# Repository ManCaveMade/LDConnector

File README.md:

## LDConnector
Copyright Mitchell A. Cox (mitch@enox.co.za)

If you use this design, please acknowledge me in any resulting publications.

### Note

v1.0 doesn't seem to work with high frequency. This is probably because the RF is connected to the case, which sucks.
v2.0 is redesigned to work with a bias driver that is on the GND side of the LD. This is "normal".
 
Designed with Eagle 7.7

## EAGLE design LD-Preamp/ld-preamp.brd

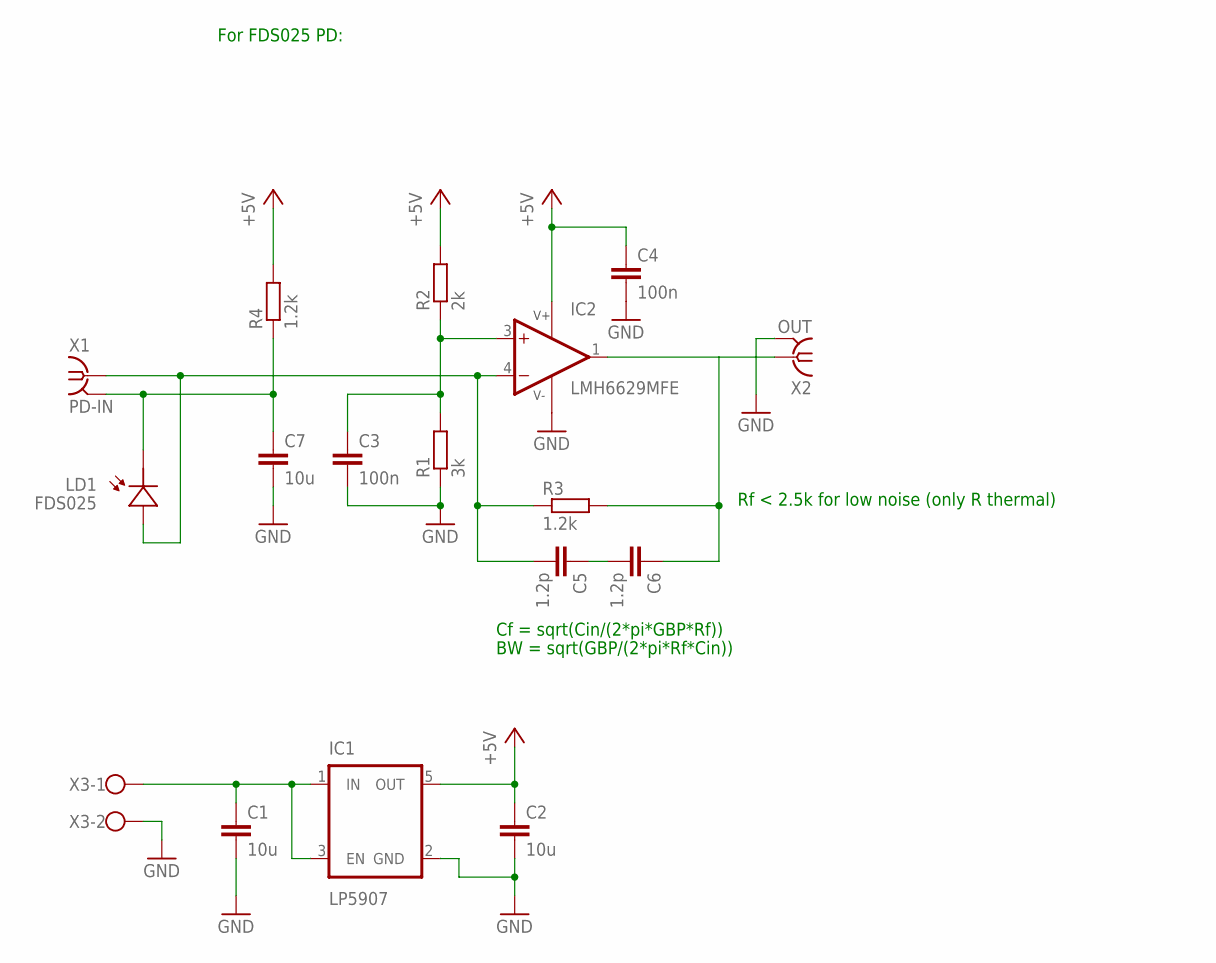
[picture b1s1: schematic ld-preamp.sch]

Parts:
C1, C2, C7: 10u; C0805
C3, C4: 100n; C0603
C5, C6: 1.2p; C0603
IC1: LP5907; SOT23-5
IC2: LMH6629MFE; SOT23-5
LD1: FDS025; PD-TO46-EDGE
R1: 3k; R0603
R2: 2k; R0603
R3, R4: 1.2k; R0603
X1: PD-IN; J502-ND-142-0711-821/826
X2: OUT; J502-ND-142-0711-821/826
X3: W237-102

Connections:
+5V: C2.1, C4.1, IC1.5 (OUT), IC2.5 (V+), R2.2, R4.2
GND: C1.2, C2.2, C3.2, C4.2, C7.2, IC1.2 (GND), IC2.2 (V-), R1.1, X2.G@1 (2), X2.G@2 (2), X2.G@3 (2), X2.G@4 (2), X3.2
unnamed: C1.1, IC1.1 (IN), IC1.3 (EN), X3.1
unnamed: C3.1, IC2.3 (+IN), R1.2, R2.1
unnamed: C5.2, IC2.4 (-IN), LD1.3 (PDA), R3.1, X1.1
unnamed: C5.1, C6.2
unnamed: C6.1, IC2.1 (OUT), R3.2, X2.1
unnamed: C7.1, LD1.1 (PDC), R4.1, X1.G@1 (2), X1.G@2 (2), X1.G@3 (2), X1.G@4 (2)

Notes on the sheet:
Cf = sqrt(Cin/(2*pi*GBP*Rf))
BW = sqrt(GBP/(2*pi*Rf*Cin))
Rf < 2.5k for low noise (only R thermal)
For FDS025 PD:

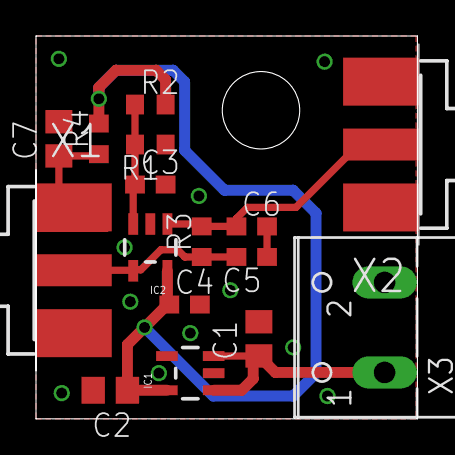
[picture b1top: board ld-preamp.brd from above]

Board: 2 copper layers, 21.3 x 21.3 mm, 17 parts (0 on the bottom side), 8 nets.

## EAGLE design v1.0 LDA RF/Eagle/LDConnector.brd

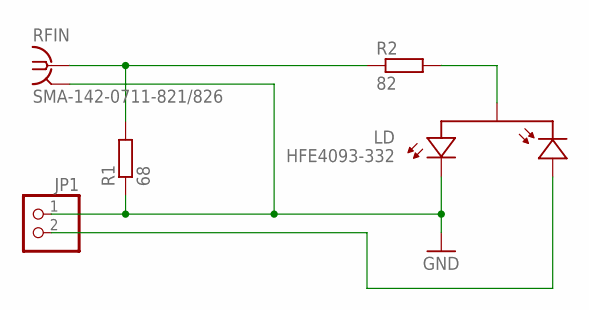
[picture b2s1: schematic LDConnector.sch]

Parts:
JP1: PINHD-1X2/90; 1X02/90
LD: HFE4093-332; HFE4093-332-EDGE
R1: 68; R0603
R2: 82; R0603
RFIN: SMA-142-0711-821/826; J502-ND-142-0711-821/826

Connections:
GND: JP1.1, LD.1-LD-CATHODE (LDC), R1.1, RFIN.G@1 (2), RFIN.G@2 (2), RFIN.G@3 (2), RFIN.G@4 (2)
unnamed: LD.2-PD-CATHODE-LD-ANO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 (LDA-PDC), R2.2
unnamed: R1.2, R2.1, RFIN.1
unnamed: JP1.2, LD.3-PD-ANODE (PDA)

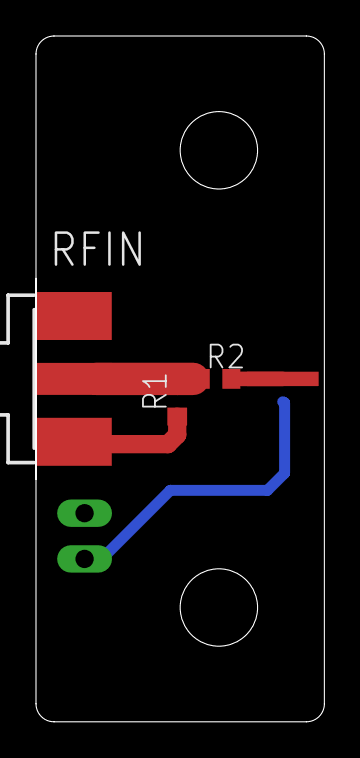
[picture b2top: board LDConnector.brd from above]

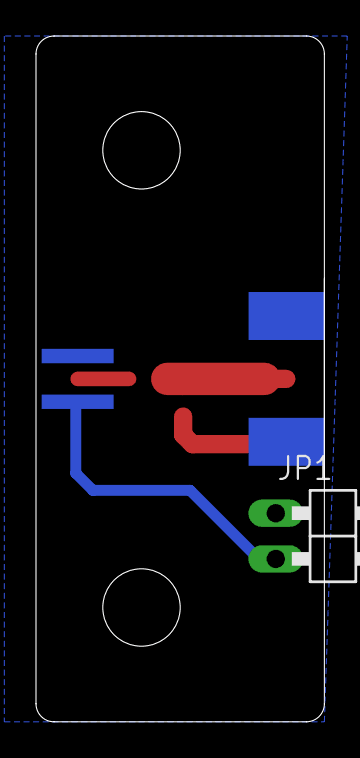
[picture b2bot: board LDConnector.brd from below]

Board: 2 copper layers, 16.0 x 38.1 mm, 5 parts (2 on the bottom side), 4 nets.

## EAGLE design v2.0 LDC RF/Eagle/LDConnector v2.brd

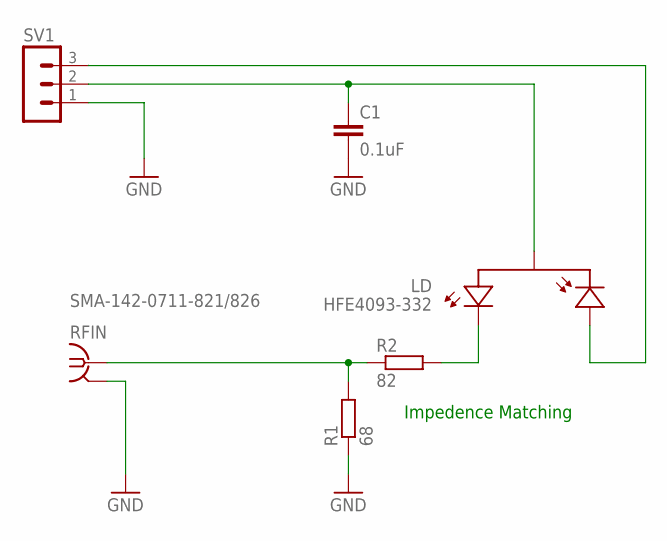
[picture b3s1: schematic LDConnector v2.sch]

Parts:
C1: 0.1uF; C0603
LD: HFE4093-332; HFE4093-332-EDGE
R1: 68; R0603
R2: 82; R0603
RFIN: SMA-142-0711-821/826; J502-ND-142-0711-821/826
SV1: MA03-1

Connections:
GND: C1.2, R1.1, RFIN.G@1 (2), RFIN.G@2 (2), RFIN.G@3 (2), RFIN.G@4 (2), SV1.1
unnamed: C1.1, LD.2-PD-CATHODE-LD-ANO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 (LDA-PDC), SV1.2
unnamed: LD.1-LD-CATHODE (LDC), R2.2
unnamed: R1.2, R2.1, RFIN.1
unnamed: LD.3-PD-ANODE (PDA), SV1.3

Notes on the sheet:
Impedence Matching

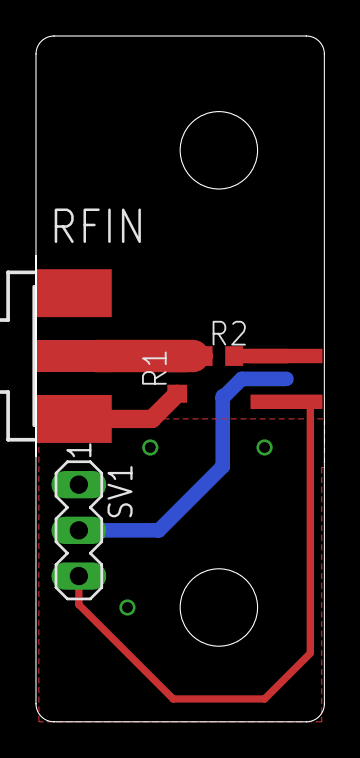
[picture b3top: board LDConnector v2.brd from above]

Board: 2 copper layers, 16.0 x 38.1 mm, 6 parts (1 on the bottom side), 5 nets.

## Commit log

2016-11-29 First commit of everything.
2017-03-05 started work on a high bandwidth, low noise preamp
